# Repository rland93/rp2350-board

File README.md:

# rp2350-board
RP2350 board with servos

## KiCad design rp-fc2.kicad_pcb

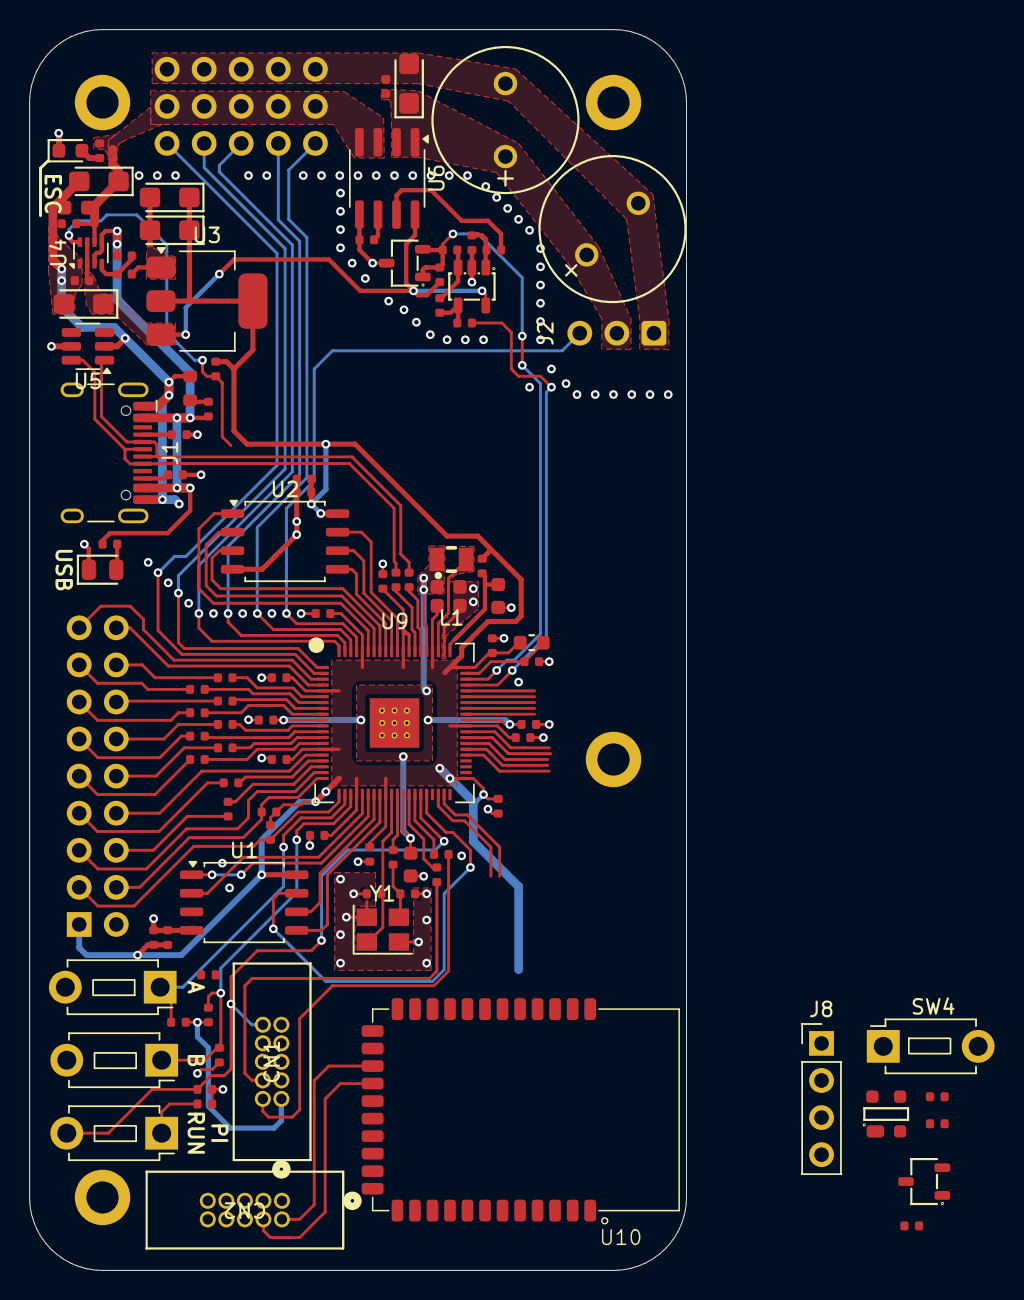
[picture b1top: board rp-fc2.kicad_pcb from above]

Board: 4 copper layers, 45.0 x 85.0 mm, 110 parts (1 on the bottom side), 88 nets.

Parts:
C1, C2, C3, C6: 4.7uF; C_0603
C4, C5, C7, C8, C9, C10, C11, C12, C13, C14, C15, C18, C19, C26, C27, C28, C31, C32, C33, C34, C35, C36, C37, C46: 100nF; C_0402
C16, C17: 15pF; C_0402
C20, C21, C22, C23, C30: 10uF; C_CASE-A-3216-18(mm)
C24, C25: 470uF; C_Plugin,D10xL16mm
C29: 2.2uF; C_0603
CN1, CN2: 20021521-00010T1LF; CONN_3220-10-0100-00_CNC
D1: Red; D_0805
D2: Red; D_0603
D3: H5VUT1B; SOT-143-4_L2.9-W1.3-P1.90-LS2.4-BL-1
FB1: FB_0603
H1, H2, H3, H4: MountingHole_Pad; MountingHole_2.2mm_M2_DIN965_Pad
J1: USB_C_Receptacle_USB2.0_16P; USB_C_Receptacle_HCTL_HC-TYPE-C-16P-01A
J2: Conn_01x03; PinHeader_1x03_P2.54mm_Vertical
J3, J4, J5: Conn_01x05; PinHeader_1x05_P2.54mm_Vertical
J6: OV7670 Breakout; PinHeader_2x09_P2.54mm_Vertical
J8: Conn_01x04; PinHeader_1x04_P2.54mm_Vertical
L1: AOTA-B201610S3R3-101-T; IND-SMD_L2.0-W1.6_AOTA-B201610S3R3-101-T
R1: 33Ω; R_0402
R2, R3, R6, R7, R23, R25, R26, R27, R28, R29, R30, R31, R32, R33: 22Ω; R_0402
R4, R5, R38: 1kΩ; R_0402
R8, R11: 5.1kΩ; R_0402
R9, R12, R13, R16, R20, R24, R36, R37: 10kΩ; R_0402
R10, R19, R22: 220Ω; R_0402
R14: 33kΩ; R_0402
R15: 82kΩ; R_0603
R17, R21: 27kΩ; R_0402
R18: 680Ω; R_0402
R34, R35: 4.7kΩ; R_0402
SW1, SW2, SW3, SW4: SW_Push; SW_PUSH_1P1T_6x3.5mm_H4.3_APEM_MJTP1243
U1, U2: W25Q128JVS; SOIC-8_5.23x5.23mm_P1.27mm
U3: AMS1117-3.3; SOT-223-3_TabPin2
U4: TPS2116DRL; SOT-583-8
U5: SRV05-4; SOT-23-6
U6: ACS712xLCTR-05B; SOIC-8_3.9x4.9mm_P1.27mm
U7: LMV321IDBVR; SOT-23-5_L3.0-W1.7-P0.95-LS2.8-BR
U8, U11: CJ431; SOT-23-3_L2.9-W1.6-P1.90-LS2.8-BR
U9: RP2350B-QFN80; RP2350B_QFN-80_EP_10.573x10.573_Pitch0.4mm
U10: MK19; MokoSmart MK19
Y1: Crystal_GND24; Crystal_SMD_3225-4Pin_3.2x2.5mm

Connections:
+1V1: C3.1, C4.1, C5.1, C6.1, L1.2, U9.10 (DVDD), U9.32 (DVDD), U9.51 (DVDD), U9.65 (VREG_FB)
+3V3: C2.1, C8.1, C9.1, C10.1, C11.1, C12.1, C13.1, C14.1, C15.1, C21.1, C22.1, C31.1, C33.1, C34.1, C36.1, C37.1, CN1.1, CN2.1, D3.4, FB1.1, J6.1, J8.1, R1.1, R13.1, R24.2, R34.1, R35.1, R36.2, R37.2, R38.2, U1.8 (VCC), U2.8 (VCC), U3.2 (VO), U9.5 (IOVDD), U9.15 (IOVDD), U9.24 (IOVDD), U9.29 (IOVDD), U9.41 (IOVDD), U9.50 (IOVDD), U9.60 (IOVDD), U9.64 (VREG_VIN), U9.68 (USB_OTP_VDD), U9.69 (QSPI_IOVDD), U9.76 (IOVDD)
+5V: C19.1, C20.1, R18.1, U3.3 (VI), U4.2 (VOUT), U4.7 (VOUT), U6.8 (VCC), U7.5 (V+)
/IO/NRF_UART_RX: D3.2, J8.3
/IO/NRF_UART_TX: D3.3, J8.2
/Power/I_SRVO_RAW: R16.1, U6.7 (VIOUT)
/Power/USB_VBUS: J1.A4 (VBUS), J1.A9 (VBUS), J1.B4 (VBUS), J1.B9 (VBUS), R9.1, R10.2, R14.1, U4.3 (VIN1), U4.5 (MODE), U5.5 (VP)
/Power/VBUCK_IN: C23.1, C24.1, C25.1, C26.1, J2.2, U6.1 (IP+), U6.2 (IP+)
/XIN: C17.1, U9.30 (XIN), Y1.1
/XOUT: R5.2, U9.31 (XOUT)
CAMERA_PWDN: J6.18, U9.4 (GPIO7)
CAMERA_RST: J6.17, U9.3 (GPIO6)
CH1: J2.1, U9.77 (GPIO0)
CH2: J3.1, U9.2 (GPIO5)
CH3: J3.2, U9.1 (GPIO4)
CH4: J3.3, U9.80 (GPIO3)
CH5: J3.4, U9.79 (GPIO2)
CH6: J3.5, U9.78 (GPIO1)
D0: J6.16, R23.2
D1: J6.15, R25.2
D2: J6.14, R26.2
D3: J6.13, R27.2
D4: J6.12, R28.2
D5: J6.11, R29.2
D6: J6.10, R30.2
D7: J6.9, R31.2
FLASH2_RESET: U1.7 (IO3), U9.36 (GPIO28)
GND: C1.2, C2.2, C3.2, C4.2, C5.2, C6.2, C7.2, C8.2, C9.2, C10.2, C11.2, C12.2, C13.2, C14.2, C15.2, C16.2, C17.2, C18.2, C19.2, C20.2, C21.2, C22.2, C23.2, C24.2, C25.2, C26.2, C27.2, C28.2, C29.2, C30.2, C31.2, C32.2, C33.2, C34.2, C35.2, C36.2, C37.2, C46.2, CN1.3, CN1.5, CN1.9, CN2.3, CN2.5, CN2.9, D1.1, D2.1, D3.1, H1.1, H2.1, H3.1, H4.1, J1.A1 (GND), J1.A12 (GND), J1.B1 (GND), J1.B12 (GND), J1.S1 (SHIELD), J2.3, J5.1, J5.2, J5.3, J5.4, J5.5, J6.2, J8.4, R4.1, R8.2, R11.2, R12.2, R15.2, R17.2, SW2.2, SW3.2, SW4.2, U1.4 (GND), U2.4 (GND), U3.1 (GND), U4.1 (GND), U5.2 (VN), U6.5 (GND), U7.2 (GND), U8.3 (A), U9.62 (VREG_PGND), U9.81 (GND), U10.10 (VSS), U11.3 (A), Y1.2, Y1.4
HREF: J6.6, R33.2
I_COND: R19.2, U9.57 (GPIO46_ADC6)
I_COND_2_5: R18.2, R20.1, U8.1 (K), U8.2 (R), U9.58 (GPIO47_ADC7)
NRF_NRESET: C46.1, CN2.10, R37.1, SW4.1, U10.33 (nRESET)
NRF_SWCLK: CN2.4, U10.19 (SWDCLK)
NRF_SWDIO: CN2.2, U10.20 (SWDIO)
unnamed: C16.1, R5.1, Y1.3
unnamed: D1.2, R10.1
unnamed: D2.2, R22.1
unnamed: J1.A5 (CC1), R8.1
unnamed: J1.B5 (CC2), R11.1
unnamed: R4.2, SW1.1
unnamed: R9.2, R12.1, U4.4 (PR1)
unnamed: C27.1, U6.6 (FILTER)
unnamed: R16.2, R17.1, U7.1 (+)
unnamed: R20.2, R21.2, U7.3 (-)
unnamed: R19.1, R21.1, U7.4 (OUT)
unnamed: R23.1, U9.6 (GPIO8)
unnamed: R25.1, U9.7 (GPIO9)
unnamed: R26.1, U9.8 (GPIO10)
unnamed: R27.1, U9.9 (GPIO11)
unnamed: R28.1, U9.11 (GPIO12)
unnamed: R29.1, U9.12 (GPIO13)
unnamed: R30.1, U9.13 (GPIO14)
unnamed: R31.1, U9.14 (GPIO15)
unnamed: R32.1, U9.17 (GPIO17)
unnamed: R33.1, U9.18 (GPIO18)
unnamed: R6.2, U9.33 (SWCLK)
unnamed: R7.2, U9.34 (SWDIO)
unnamed: R3.1, U9.66 (USB_DM)
unnamed: R2.1, U9.67 (USB_DP)
unnamed: C1.1, R1.2, U9.61 (VREG_AVDD)
unnamed: L1.1, U9.63 (VREG_LX)
unnamed: R38.1, U10.17 (P1.08/CLK16M/EXTREF), U11.1 (K), U11.2 (R)
OTG_FS_VBUS: R14.2, R15.1
PCLK: J6.7, R32.2
PWR_STATUS: R13.2, U4.8 (ST)
QSPI_CLK: U2.6 (CLK), U9.71 (QSPI_SCLK)
QSPI_CS: U2.1 (~CS), U9.75 (QSPI_SS)
QSPI_SD1: U2.2 (DO(IO1)), U9.74 (QSPI_SD1)
QSPI_SD2: U2.3 (IO2), U9.73 (QSPI_SD2)
QSPI_SD3: U2.7 (IO3), U9.70 (QSPI_SD3)
QSPI_SDO: U2.5 (DI(IO0)), U9.72 (QSPI_SD0)
RP2350_RUN: C18.1, CN1.10, SW1.2, U9.35 (RUN)
SIO_C: J6.3, R35.2, U9.21 (GPIO21)
SIO_D: J6.4, R34.2, U9.20 (GPIO20)
SPI1_CS1: U1.1 (~CS), U9.26 (GPIO25)
SPI1_MISO: U1.2 (DO(IO1)), U9.25 (GPIO24)
SPI1_MOSI: U1.5 (DI(IO0)), U9.28 (GPIO27)
SPI1_SCK: U1.6 (CLK), U9.27 (GPIO26)
SWCLK: CN1.4, R6.1
SWDIO: CN1.2, R7.1
USB_D+: J1.A6 (D+), J1.B6 (D+), R2.2, U5.6 (IO4)
USB_D-: J1.A7 (D-), J1.B7 (D-), R3.2, U5.1 (IO1)
USR_SW1: C32.1, R24.1, SW3.1, U9.22 (GPIO22)
USR_SW2: C35.1, R36.1, SW2.1, U9.23 (GPIO23)
VBUCK: C28.1, C29.1, C30.1, J4.1, J4.2, J4.3, J4.4, J4.5, R22.2, U4.6 (VIN2), U6.3 (IP-), U6.4 (IP-)
VDDA: C7.1, FB1.2, U9.59 (ADC_AVDD)
VSYNC: J6.5, U9.19 (GPIO19)
XCLK: J6.8, U9.16 (GPIO16)

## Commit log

2025-04-12 rp2350 basic design
2025-04-12 gitignore
2025-04-12 rp2350 power + servo rails
2025-04-12 3v3 rail thicker
2025-04-12 PCB review images and PDF
2025-04-12 3d board view
2025-04-15 add camera breakout
2025-04-17 rp2350B -- larger package
2025-04-19 nrf52833-discrete
2025-04-27 nrf54L BLE module
